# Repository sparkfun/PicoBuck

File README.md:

PicoBuck LED Driver
===================

[  
*PicoBuck LED Driver (COM-11850)*](https://www.sparkfun.com/products/11850)

This breakout board allows you to control and blend 3 different LEDs on 3 different channels. 

Repository Contents
-------------------
* **/Hardware** - All Eagle design files (.brd, .sch, .STL)
* **/Production** - Test bed files and production panel files

License Information
-------------------
The hardware is released under [Creative Commons Share-alike 3.0](http://creativecommons.org/licenses/by-sa/3.0/).  
All other code is open source so please feel free to do anything you want with it; you buy me a beer if you use this and we meet someday ([Beerware license](http://en.wikipedia.org/wiki/Beerware)).
 
 -> This was a collaboration with Ethan Zonca<-

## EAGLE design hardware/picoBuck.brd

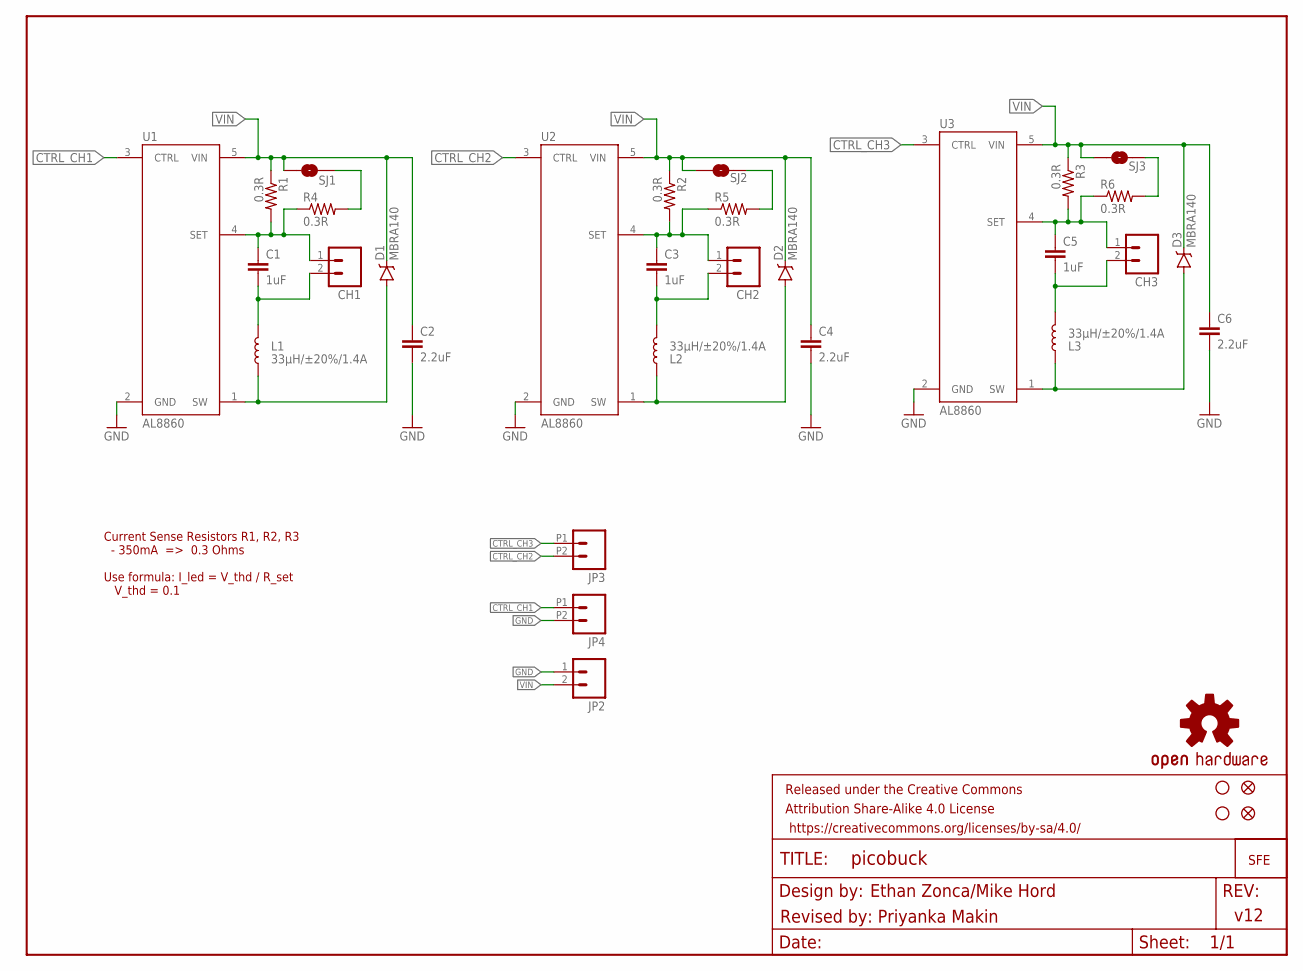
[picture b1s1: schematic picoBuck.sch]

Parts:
C1, C3, C5: 1uF; 0805
C2, C4, C6: 2.2uF; 0805
CH1, CH2, CH3: CONN_023.5MM_LOCK; SCREWTERMINAL-3.5MM-2_LOCK
D1, D2, D3: MBRA140; SMA-DIODE
FID1, FID2: FIDUCIALUFIDUCIAL; MICRO-FIDUCIAL
FRAME1: FRAME-LETTER; CREATIVE_COMMONS
JP2: CONN_023.5MM_LOCK; SCREWTERMINAL-3.5MM-2_LOCK
JP3, JP4: M022.54MM_SCREWTERM; 1X02_2.54_SCREWTERM@1
L1, L2, L3: 33µH/±20%/1.4A; SRN6045
LOGO1: OSHW-LOGOS; OSHW-LOGO-S
LOGO2: LOGO-SFENEW; SFE-NEW-WEBLOGO
R1, R2, R3, R4, R5, R6: 0.3R; 0805
SJ1, SJ2, SJ3: JUMPER-SMT_2_NO_NO-SILK; SMT-JUMPER_2_NO_NO-SILK
STANDOFF1, STANDOFF2: STAND-OFF
U1, U2, U3: AL8860; SOT23-5

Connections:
CTRL_CH1: JP4.P1 (1), U1.3 (CTRL)
CTRL_CH2: JP3.P2 (2), U2.3 (CTRL)
CTRL_CH3: JP3.P1 (1), U3.3 (CTRL)
GND: C2.2, C4.2, C6.2, JP2.1, JP4.P2 (2), U1.2 (GND), U2.2 (GND), U3.2 (GND)
IND1-1: D1.A, L1.1, U1.1 (SW)
IND2-1: D2.A, L2.1, U2.1 (SW)
IND3-1: D3.A, L3.1, U3.1 (SW)
unnamed: C5.1, CH3.1, R3.2, R6.1, U3.4 (SET)
unnamed: R4.2, SJ1.2
unnamed: R5.2, SJ2.2
unnamed: C1.2, CH1.2, L1.2
unnamed: R6.2, SJ3.2
unnamed: C3.2, CH2.2, L2.2
unnamed: C1.1, CH1.1, R1.2, R4.1, U1.4 (SET)
unnamed: C3.1, CH2.1, R2.2, R5.1, U2.4 (SET)
unnamed: C5.2, CH3.2, L3.2
VIN: C2.1, C4.1, C6.1, D1.C, D2.C, D3.C, JP2.2, R1.1, R2.1, R3.1, SJ1.1, SJ2.1, SJ3.1, U1.5 (VIN), U2.5 (VIN), U3.5 (VIN)

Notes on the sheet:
Current Sense Resistors R1, R2, R3 - 350mA => 0.3 Ohms Use formula: I_led = V_thd / R_set V_thd = 0.1
v12
Ethan Zonca/Mike Hord
Revised by: Priyanka Makin

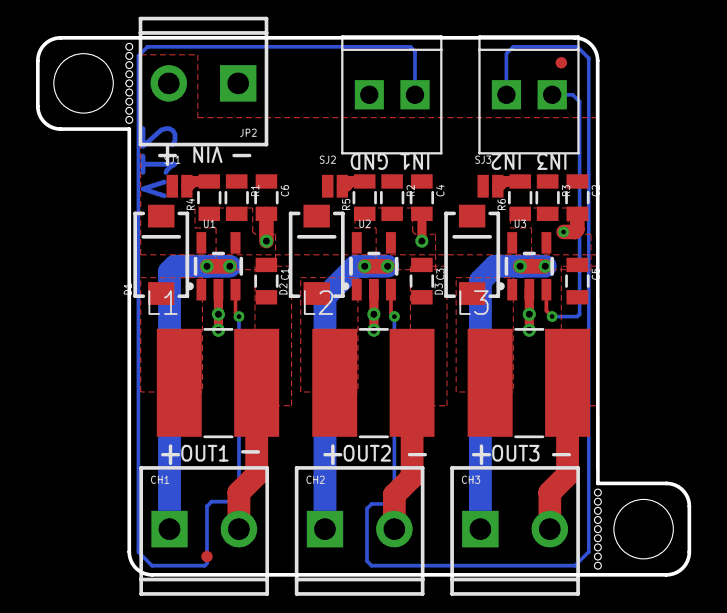
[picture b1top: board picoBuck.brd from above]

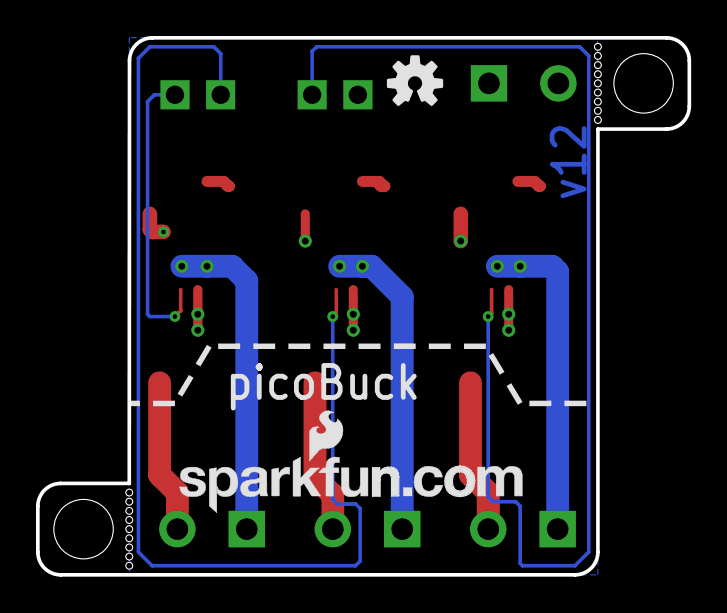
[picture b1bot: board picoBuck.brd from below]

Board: 2 copper layers, 36.2 x 29.8 mm, 37 parts (2 on the bottom side), 17 nets.

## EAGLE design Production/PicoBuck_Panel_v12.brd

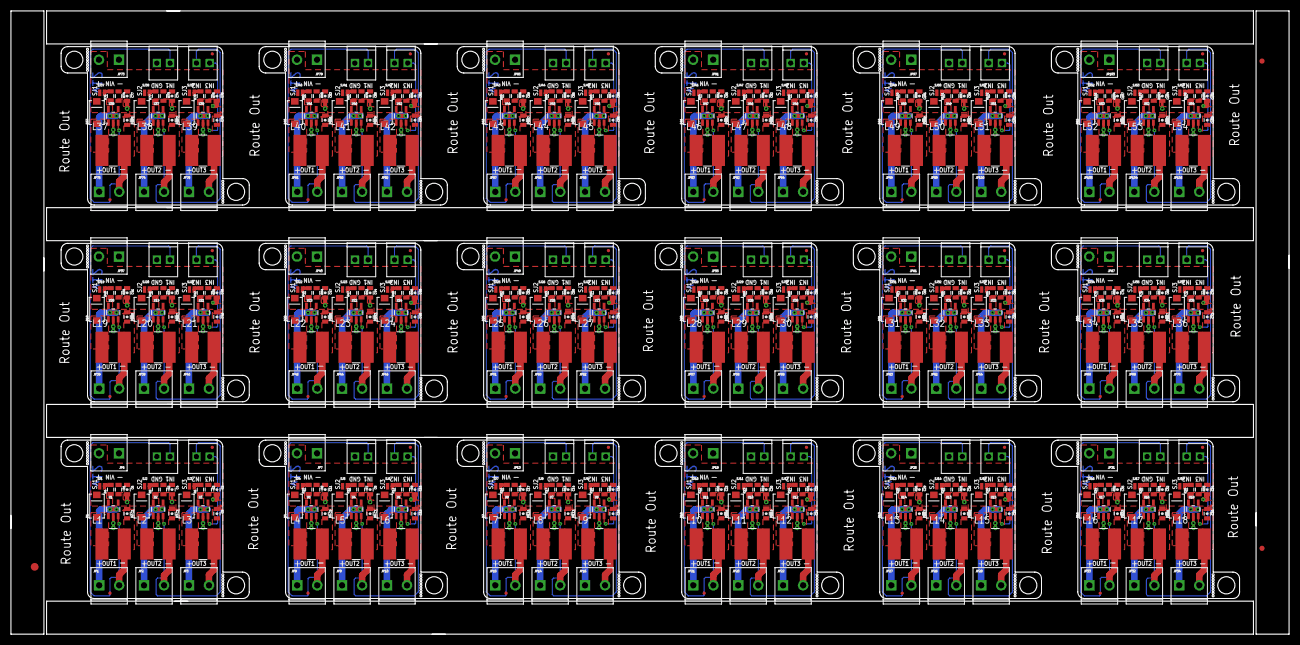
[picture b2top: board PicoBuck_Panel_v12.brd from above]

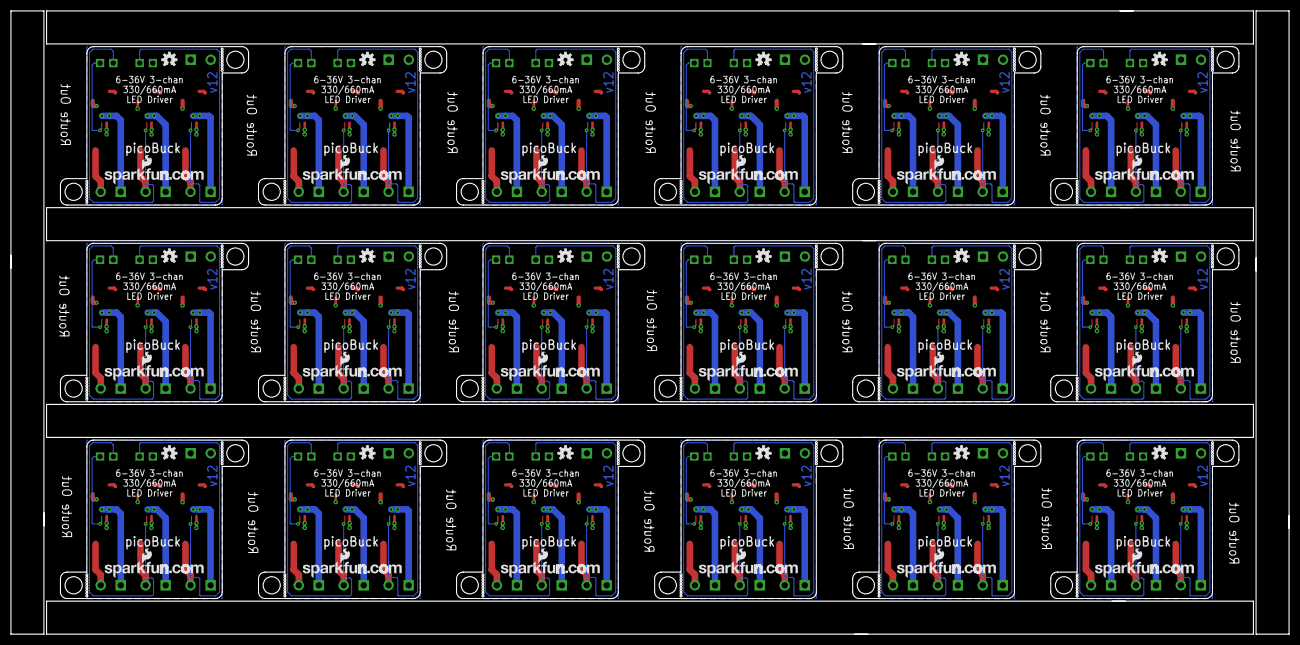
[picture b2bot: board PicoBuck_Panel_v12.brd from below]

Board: 2 copper layers, 245.9 x 119.9 mm, 651 parts (36 on the bottom side), 306 nets.

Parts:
C1, C3, C5, C7, C9, C12, C13, C15, C18, C19, C21, C24, C25, C27, C30, C31, C33, C36, C37, C39, C42, C43, C45, C48, C49, C51, C54, C55, C57, C60, C61, C63, C66, C67, C69, C72, C73, C75, C78, C79, C81, C84, C85, C87, C90, C91, C93, C96, C97, C99, C102, C103, C105, C108: 1.0uF; 0805-CAP
C2, C4, C6, C8, C10, C11, C14, C16, C17, C20, C22, C23, C26, C28, C29, C32, C34, C35, C38, C40, C41, C44, C46, C47, C50, C52, C53, C56, C58, C59, C62, C64, C65, C68, C70, C71, C74, C76, C77, C80, C82, C83, C86, C88, C89, C92, C94, C95, C98, C100, C101, C104, C106, C107: 2.2uF; 0805-CAP
D1, D2, D3, D4, D5, D6, D7, D8, D9, D10, D11, D12, D13, D14, D15, D16, D17, D18, D19, D20, D21, D22, D23, D24, D25, D26, D27, D28, D29, D30, D31, D32, D33, D34, D35, D36, D37, D38, D39, D40, D41, D42, D43, D44, D45, D46, D47, D48, D49, D50, D51, D52, D53, D54: MBRA140; SMA-DIODE
E$1: FIDUCIAL-1.5X3
E$9, E$10: FIDUCIAL-1X2
FID1, FID2, FID3, FID4, FID5, FID6, FID7, FID8, FID9, FID10, FID11, FID12, FID13, FID14, FID15, FID16, FID17, FID18, FID19, FID20, FID21, FID22, FID23, FID24, FID25, FID26, FID27, FID28, FID29, FID30, FID31, FID32, FID33, FID34, FID35, FID36: FIDUCIALUFIDUCIAL; MICRO-FIDUCIAL
JP1, JP2, JP3, JP6, JP7, JP8, JP9, JP10, JP13, JP14, JP15, JP16, JP19, JP20, JP21, JP22, JP25, JP26, JP27, JP28, JP31, JP32, JP33, JP34, JP37, JP38, JP39, JP40, JP43, JP44, JP45, JP46, JP49, JP50, JP51, JP52, JP55, JP56, JP57, JP58, JP61, JP62, JP63, JP64, JP67, JP68, JP69, JP70, JP73, JP74, JP75, JP76, JP79, JP80, JP81, JP82, JP85, JP86, JP87, JP88, JP91, JP92, JP93, JP94, JP97, JP98, JP99, JP100, JP103, JP104, JP105, JP106: SCREWTERMINAL-3.5MM-2_LOCK
JP4, JP5, JP11, JP12, JP17, JP18, JP23, JP24, JP29, JP30, JP35, JP36, JP41, JP42, JP47, JP48, JP53, JP54, JP59, JP60, JP65, JP66, JP71, JP72, JP77, JP78, JP83, JP84, JP89, JP90, JP95, JP96, JP101, JP102, JP107, JP108: M022.54MM_SCREWTERM; 1X02_2.54_SCREWTERM
L1, L2, L3, L4, L5, L6, L7, L8, L9, L10, L11, L12, L13, L14, L15, L16, L17, L18, L19, L20, L21, L22, L23, L24, L25, L26, L27, L28, L29, L30, L31, L32, L33, L34, L35, L36, L37, L38, L39, L40, L41, L42, L43, L44, L45, L46, L47, L48, L49, L50, L51, L52, L53, L54: 33uH; SRN6045
LOGO1, LOGO3, LOGO5, LOGO7, LOGO9, LOGO11, LOGO13, LOGO15, LOGO17, LOGO19, LOGO21, LOGO23, LOGO25, LOGO27, LOGO29, LOGO31, LOGO33, LOGO35: OSHW-LOGOS; OSHW-LOGO-S
LOGO2, LOGO4, LOGO6, LOGO8, LOGO10, LOGO12, LOGO14, LOGO16, LOGO18, LOGO20, LOGO22, LOGO24, LOGO26, LOGO28, LOGO30, LOGO32, LOGO34, LOGO36: LOGO-SFENEW; SFE-NEW-WEBLOGO
R1, R2, R3, R4, R5, R6, R7, R8, R9, R10, R11, R12, R13, R14, R15, R16, R17, R18, R19, R20, R21, R22, R23, R24, R25, R26, R27, R28, R29, R30, R31, R32, R33, R34, R35, R36, R37, R38, R39, R40, R41, R42, R43, R44, R45, R46, R47, R48, R49, R50, R51, R52, R53, R54, R55, R56, R57, R58, R59, R60, R61, R62, R63, R64, R65, R66, R67, R68, R69, R70, R71, R72, R73, R74, R75, R76, R77, R78, R79, R80, R81, R82, R83, R84, R85, R86, R87, R88, R89, R90, R91, R92, R93, R94, R95, R96, R97, R98, R99, R100, R101, R102, R103, R104, R105, R106, R107, R108: 0.3; 0805
SJ1, SJ2, SJ3, SJ4, SJ5, SJ6, SJ7, SJ8, SJ9, SJ10, SJ11, SJ12, SJ13, SJ14, SJ15, SJ16, SJ17, SJ18, SJ19, SJ20, SJ21, SJ22, SJ23, SJ24, SJ25, SJ26, SJ27, SJ28, SJ29, SJ30, SJ31, SJ32, SJ33, SJ34, SJ35, SJ36, SJ37, SJ38, SJ39, SJ40, SJ41, SJ42, SJ43, SJ44, SJ45, SJ46, SJ47, SJ48, SJ49, SJ50, SJ51, SJ52, SJ53, SJ54: JUMPER-PAD-2-NO; PAD-JUMPER-2-NO_NO_SILK
STANDOFF1, STANDOFF2, STANDOFF3, STANDOFF4, STANDOFF5, STANDOFF6, STANDOFF7, STANDOFF8, STANDOFF9, STANDOFF10, STANDOFF11, STANDOFF12, STANDOFF13, STANDOFF14, STANDOFF15, STANDOFF16, STANDOFF17, STANDOFF18, STANDOFF19, STANDOFF20, STANDOFF21, STANDOFF22, STANDOFF23, STANDOFF24, STANDOFF25, STANDOFF26, STANDOFF27, STANDOFF28, STANDOFF29, STANDOFF30, STANDOFF31, STANDOFF32, STANDOFF33, STANDOFF34, STANDOFF35, STANDOFF36: STAND-OFF
U1, U2, U3, U4, U5, U6, U7, U8, U9, U10, U11, U12, U13, U14, U15, U16, U17, U18, U19, U20, U21, U22, U23, U24, U25, U26, U27, U28, U29, U30, U31, U32, U33, U34, U35, U36, U37, U38, U39, U40, U41, U42, U43, U44, U45, U46, U47, U48, U49, U50, U51, U52, U53, U54: AL8805WS; SOT23-5

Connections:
CTRL_CH1: JP5.P1, U1.3
CTRL_CH2: JP4.P2, U2.3
CTRL_CH3: JP4.P1, U3.3
CTRL_CH4: JP12.P1, U5.3
CTRL_CH5: JP11.P2, U4.3
CTRL_CH6: JP11.P1, U6.3
CTRL_CH7: JP18.P1, U8.3
CTRL_CH8: JP17.P2, U7.3
CTRL_CH9: JP17.P1, U9.3
CTRL_CH10: JP24.P1, U11.3
CTRL_CH11: JP23.P2, U10.3
CTRL_CH12: JP23.P1, U12.3
CTRL_CH13: JP30.P1, U14.3
CTRL_CH14: JP29.P2, U13.3
CTRL_CH15: JP29.P1, U15.3
CTRL_CH16: JP36.P1, U17.3
CTRL_CH17: JP35.P2, U16.3
CTRL_CH18: JP35.P1, U18.3
CTRL_CH19: JP42.P1, U20.3
CTRL_CH20: JP41.P2, U19.3
CTRL_CH21: JP41.P1, U21.3
CTRL_CH22: JP48.P1, U23.3
CTRL_CH23: JP47.P2, U22.3
CTRL_CH24: JP47.P1, U24.3
CTRL_CH25: JP54.P1, U26.3
CTRL_CH26: JP53.P2, U25.3
CTRL_CH27: JP53.P1, U27.3
CTRL_CH28: JP60.P1, U29.3
CTRL_CH29: JP59.P2, U28.3
CTRL_CH30: JP59.P1, U30.3
CTRL_CH31: JP66.P1, U32.3
CTRL_CH32: JP65.P2, U31.3
CTRL_CH33: JP65.P1, U33.3
CTRL_CH34: JP72.P1, U35.3
CTRL_CH35: JP71.P2, U34.3
CTRL_CH36: JP71.P1, U36.3
CTRL_CH37: JP78.P1, U38.3
CTRL_CH38: JP77.P2, U37.3
CTRL_CH39: JP77.P1, U39.3
CTRL_CH40: JP84.P1, U41.3
CTRL_CH41: JP83.P2, U40.3
CTRL_CH42: JP83.P1, U42.3
CTRL_CH43: JP90.P1, U44.3
CTRL_CH44: JP89.P2, U43.3
CTRL_CH45: JP89.P1, U45.3
CTRL_CH46: JP96.P1, U47.3
CTRL_CH47: JP95.P2, U46.3
CTRL_CH48: JP95.P1, U48.3
CTRL_CH49: JP102.P1, U50.3
CTRL_CH50: JP101.P2, U49.3
CTRL_CH51: JP101.P1, U51.3
CTRL_CH52: JP108.P1, U53.3
CTRL_CH53: JP107.P2, U52.3
CTRL_CH54: JP107.P1, U54.3
GND: C2.2, C4.2, C6.2, JP5.P2, JP6.1, U1.2, U2.2, U3.2
GND1: C8.2, C10.2, C11.2, JP7.1, JP12.P2, U4.2, U5.2, U6.2
GND2: C14.2, C16.2, C17.2, JP13.1, JP18.P2, U7.2, U8.2, U9.2
GND3: C20.2, C22.2, C23.2, JP19.1, JP24.P2, U10.2, U11.2, U12.2
GND4: C26.2, C28.2, C29.2, JP25.1, JP30.P2, U13.2, U14.2, U15.2
GND5: C32.2, C34.2, C35.2, JP31.1, JP36.P2, U16.2, U17.2, U18.2
GND6: C38.2, C40.2, C41.2, JP37.1, JP42.P2, U19.2, U20.2, U21.2
GND7: C44.2, C46.2, C47.2, JP43.1, JP48.P2, U22.2, U23.2, U24.2
GND8: C50.2, C52.2, C53.2, JP49.1, JP54.P2, U25.2, U26.2, U27.2
GND9: C56.2, C58.2, C59.2, JP55.1, JP60.P2, U28.2, U29.2, U30.2
GND10: C62.2, C64.2, C65.2, JP61.1, JP66.P2, U31.2, U32.2, U33.2
GND11: C68.2, C70.2, C71.2, JP67.1, JP72.P2, U34.2, U35.2, U36.2
GND12: C74.2, C76.2, C77.2, JP73.1, JP78.P2, U37.2, U38.2, U39.2
GND13: C80.2, C82.2, C83.2, JP79.1, JP84.P2, U40.2, U41.2, U42.2
GND14: C86.2, C88.2, C89.2, JP85.1, JP90.P2, U43.2, U44.2, U45.2
GND15: C92.2, C94.2, C95.2, JP91.1, JP96.P2, U46.2, U47.2, U48.2
GND16: C98.2, C100.2, C101.2, JP97.1, JP102.P2, U49.2, U50.2, U51.2
GND17: C104.2, C106.2, C107.2, JP103.1, JP108.P2, U52.2, U53.2, U54.2
IND1-1: D1.A, L1.1, U1.1
IND1-2: D4.A, L4.1, U5.1
IND1-3: D7.A, L7.1, U8.1
IND1-4: D10.A, L10.1, U11.1
IND1-5: D13.A, L13.1, U14.1
IND1-6: D16.A, L16.1, U17.1
IND1-7: D19.A, L19.1, U20.1
IND1-8: D22.A, L22.1, U23.1
IND1-9: D25.A, L25.1, U26.1
IND1-10: D28.A, L28.1, U29.1
IND1-11: D31.A, L31.1, U32.1
IND1-12: D34.A, L34.1, U35.1
IND1-13: D37.A, L37.1, U38.1
IND1-14: D40.A, L40.1, U41.1
IND1-15: D43.A, L43.1, U44.1
IND1-16: D46.A, L46.1, U47.1
IND1-17: D49.A, L49.1, U50.1
IND1-18: D52.A, L52.1, U53.1
IND2-1: D2.A, L2.1, U2.1
IND2-2: D5.A, L5.1, U4.1
IND2-3: D8.A, L8.1, U7.1
IND2-4: D11.A, L11.1, U10.1
IND2-5: D14.A, L14.1, U13.1
IND2-6: D17.A, L17.1, U16.1
IND2-7: D20.A, L20.1, U19.1
IND2-8: D23.A, L23.1, U22.1
IND2-9: D26.A, L26.1, U25.1
IND2-10: D29.A, L29.1, U28.1
IND2-11: D32.A, L32.1, U31.1
IND2-12: D35.A, L35.1, U34.1
IND2-13: D38.A, L38.1, U37.1
IND2-14: D41.A, L41.1, U40.1
IND2-15: D44.A, L44.1, U43.1
IND2-16: D47.A, L47.1, U46.1
IND2-17: D50.A, L50.1, U49.1
IND2-18: D53.A, L53.1, U52.1
IND3-1: D3.A, L3.1, U3.1
IND3-2: D6.A, L6.1, U6.1
IND3-3: D9.A, L9.1, U9.1
IND3-4: D12.A, L12.1, U12.1
IND3-5: D15.A, L15.1, U15.1
IND3-6: D18.A, L18.1, U18.1
IND3-7: D21.A, L21.1, U21.1
IND3-8: D24.A, L24.1, U24.1
IND3-9: D27.A, L27.1, U27.1
IND3-10: D30.A, L30.1, U30.1
IND3-11: D33.A, L33.1, U33.1
IND3-12: D36.A, L36.1, U36.1
IND3-13: D39.A, L39.1, U39.1
IND3-14: D42.A, L42.1, U42.1
IND3-15: D45.A, L45.1, U45.1
IND3-16: D48.A, L48.1, U48.1
IND3-17: D51.A, L51.1, U51.1
IND3-18: D54.A, L54.1, U54.1
unnamed: C5.1, JP3.1, R3.2, R6.1, U3.4
unnamed: R4.2, SJ1.2
unnamed: R5.2, SJ2.2
unnamed: C7.2, JP8.2, L5.2
unnamed: C1.2, JP1.2, L1.2
unnamed: C7.1, JP8.1, R7.2, R11.1, U4.4
unnamed: R6.2, SJ3.2
unnamed: C9.2, JP9.2, L4.2
unnamed: C3.2, JP2.2, L2.2
unnamed: C9.1, JP9.1, R8.2, R10.1, U5.4
unnamed: C1.1, JP1.1, R1.2, R4.1, U1.4
unnamed: C12.2, JP10.2, L6.2
unnamed: C3.1, JP2.1, R2.2, R5.1, U2.4
unnamed: R10.2, SJ4.2
unnamed: R11.2, SJ5.2
unnamed: C5.2, JP3.2, L3.2
unnamed: R12.2, SJ6.2
unnamed: C12.1, JP10.1, R9.2, R12.1, U6.4
unnamed: C13.2, JP14.2, L8.2
unnamed: C13.1, JP14.1, R13.2, R17.1, U7.4
unnamed: C15.2, JP15.2, L7.2
unnamed: C15.1, JP15.1, R14.2, R16.1, U8.4
unnamed: C18.2, JP16.2, L9.2
unnamed: R16.2, SJ7.2
unnamed: R17.2, SJ8.2
unnamed: R18.2, SJ9.2
unnamed: C18.1, JP16.1, R15.2, R18.1, U9.4
unnamed: C19.2, JP20.2, L11.2
unnamed: C19.1, JP20.1, R19.2, R23.1, U10.4
unnamed: C21.2, JP21.2, L10.2
unnamed: C21.1, JP21.1, R20.2, R22.1, U11.4
unnamed: C24.2, JP22.2, L12.2
unnamed: R22.2, SJ10.2
unnamed: R23.2, SJ11.2
unnamed: R24.2, SJ12.2
unnamed: C24.1, JP22.1, R21.2, R24.1, U12.4
unnamed: C25.2, JP26.2, L14.2
unnamed: C25.1, JP26.1, R25.2, R29.1, U13.4
unnamed: C27.2, JP27.2, L13.2
unnamed: C27.1, JP27.1, R26.2, R28.1, U14.4
unnamed: C30.2, JP28.2, L15.2
unnamed: R28.2, SJ13.2
unnamed: R29.2, SJ14.2
unnamed: R30.2, SJ15.2
unnamed: C30.1, JP28.1, R27.2, R30.1, U15.4
unnamed: C31.2, JP32.2, L17.2
unnamed: C31.1, JP32.1, R31.2, R35.1, U16.4
unnamed: C33.2, JP33.2, L16.2
unnamed: C33.1, JP33.1, R32.2, R34.1, U17.4
unnamed: C36.2, JP34.2, L18.2
unnamed: R34.2, SJ16.2
unnamed: R35.2, SJ17.2
unnamed: R36.2, SJ18.2
unnamed: C36.1, JP34.1, R33.2, R36.1, U18.4
unnamed: C37.2, JP38.2, L20.2
unnamed: C37.1, JP38.1, R37.2, R41.1, U19.4
unnamed: C39.2, JP39.2, L19.2
unnamed: C39.1, JP39.1, R38.2, R40.1, U20.4
unnamed: C42.2, JP40.2, L21.2
unnamed: R40.2, SJ19.2
unnamed: R41.2, SJ20.2
unnamed: R42.2, SJ21.2
unnamed: C42.1, JP40.1, R39.2, R42.1, U21.4
unnamed: C43.2, JP44.2, L23.2
unnamed: C43.1, JP44.1, R43.2, R47.1, U22.4
unnamed: C45.2, JP45.2, L22.2
unnamed: C45.1, JP45.1, R44.2, R46.1, U23.4
unnamed: C48.2, JP46.2, L24.2
unnamed: R46.2, SJ22.2
unnamed: R47.2, SJ23.2
unnamed: R48.2, SJ24.2
unnamed: C48.1, JP46.1, R45.2, R48.1, U24.4
unnamed: C49.2, JP50.2, L26.2
unnamed: C49.1, JP50.1, R49.2, R53.1, U25.4
unnamed: C51.2, JP51.2, L25.2
unnamed: C51.1, JP51.1, R50.2, R52.1, U26.4
unnamed: C54.2, JP52.2, L27.2
unnamed: R52.2, SJ25.2
unnamed: R53.2, SJ26.2
unnamed: R54.2, SJ27.2
unnamed: C54.1, JP52.1, R51.2, R54.1, U27.4
unnamed: C55.2, JP56.2, L29.2
unnamed: C55.1, JP56.1, R55.2, R59.1, U28.4
unnamed: C57.2, JP57.2, L28.2
unnamed: C57.1, JP57.1, R56.2, R58.1, U29.4
unnamed: C60.2, JP58.2, L30.2
unnamed: R58.2, SJ28.2
unnamed: R59.2, SJ29.2
unnamed: R60.2, SJ30.2
unnamed: C60.1, JP58.1, R57.2, R60.1, U30.4
unnamed: C61.2, JP62.2, L32.2
unnamed: C61.1, JP62.1, R61.2, R65.1, U31.4
unnamed: C63.2, JP63.2, L31.2
unnamed: C63.1, JP63.1, R62.2, R64.1, U32.4
unnamed: C66.2, JP64.2, L33.2
unnamed: R64.2, SJ31.2
unnamed: R65.2, SJ32.2
unnamed: R66.2, SJ33.2
unnamed: C66.1, JP64.1, R63.2, R66.1, U33.4
unnamed: C67.2, JP68.2, L35.2
unnamed: C67.1, JP68.1, R67.2, R71.1, U34.4
unnamed: C69.2, JP69.2, L34.2
unnamed: C69.1, JP69.1, R68.2, R70.1, U35.4
unnamed: C72.2, JP70.2, L36.2
unnamed: R70.2, SJ34.2
unnamed: R71.2, SJ35.2
unnamed: R72.2, SJ36.2
unnamed: C72.1, JP70.1, R69.2, R72.1, U36.4
unnamed: C73.2, JP74.2, L38.2
unnamed: C73.1, JP74.1, R73.2, R77.1, U37.4
unnamed: C75.2, JP75.2, L37.2
unnamed: C75.1, JP75.1, R74.2, R76.1, U38.4
unnamed: C78.2, JP76.2, L39.2
unnamed: R76.2, SJ37.2
unnamed: R77.2, SJ38.2
unnamed: R78.2, SJ39.2
unnamed: C78.1, JP76.1, R75.2, R78.1, U39.4
unnamed: C79.2, JP80.2, L41.2
unnamed: C79.1, JP80.1, R79.2, R83.1, U40.4
unnamed: C81.2, JP81.2, L40.2
unnamed: C81.1, JP81.1, R80.2, R82.1, U41.4
unnamed: C84.2, JP82.2, L42.2
unnamed: R82.2, SJ40.2
unnamed: R83.2, SJ41.2
unnamed: R84.2, SJ42.2
unnamed: C84.1, JP82.1, R81.2, R84.1, U42.4
unnamed: C85.2, JP86.2, L44.2
unnamed: C85.1, JP86.1, R85.2, R89.1, U43.4
unnamed: C87.2, JP87.2, L43.2
unnamed: C87.1, JP87.1, R86.2, R88.1, U44.4
unnamed: C90.2, JP88.2, L45.2
unnamed: R88.2, SJ43.2
unnamed: R89.2, SJ44.2
unnamed: R90.2, SJ45.2
unnamed: C90.1, JP88.1, R87.2, R90.1, U45.4
unnamed: C91.2, JP92.2, L47.2
unnamed: C91.1, JP92.1, R91.2, R95.1, U46.4
unnamed: C93.2, JP93.2, L46.2
unnamed: C93.1, JP93.1, R92.2, R94.1, U47.4
unnamed: C96.2, JP94.2, L48.2
unnamed: R94.2, SJ46.2
unnamed: R95.2, SJ47.2
unnamed: R96.2, SJ48.2
unnamed: C96.1, JP94.1, R93.2, R96.1, U48.4
unnamed: C97.2, JP98.2, L50.2
unnamed: C97.1, JP98.1, R97.2, R101.1, U49.4
unnamed: C99.2, JP99.2, L49.2
unnamed: C99.1, JP99.1, R98.2, R100.1, U50.4
unnamed: C102.2, JP100.2, L51.2
unnamed: R100.2, SJ49.2
unnamed: R101.2, SJ50.2
unnamed: R102.2, SJ51.2
unnamed: C102.1, JP100.1, R99.2, R102.1, U51.4
unnamed: C103.2, JP104.2, L53.2
unnamed: C103.1, JP104.1, R103.2, R107.1, U52.4
unnamed: C105.2, JP105.2, L52.2
unnamed: C105.1, JP105.1, R104.2, R106.1, U53.4
unnamed: C108.2, JP106.2, L54.2
unnamed: R106.2, SJ52.2
unnamed: R107.2, SJ53.2
unnamed: R108.2, SJ54.2
unnamed: C108.1, JP106.1, R105.2, R108.1, U54.4
VIN: C2.1, C4.1, C6.1, D1.C, D2.C, D3.C, JP6.2, R1.1, R2.1, R3.1, SJ1.1, SJ2.1, SJ3.1, U1.5, U2.5, U3.5
VIN1: C8.1, C10.1, C11.1, D4.C, D5.C, D6.C, JP7.2, R7.1, R8.1, R9.1, SJ4.1, SJ5.1, SJ6.1, U4.5, U5.5, U6.5
VIN2: C14.1, C16.1, C17.1, D7.C, D8.C, D9.C, JP13.2, R13.1, R14.1, R15.1, SJ7.1, SJ8.1, SJ9.1, U7.5, U8.5, U9.5
VIN3: C20.1, C22.1, C23.1, D10.C, D11.C, D12.C, JP19.2, R19.1, R20.1, R21.1, SJ10.1, SJ11.1, SJ12.1, U10.5, U11.5, U12.5
VIN4: C26.1, C28.1, C29.1, D13.C, D14.C, D15.C, JP25.2, R25.1, R26.1, R27.1, SJ13.1, SJ14.1, SJ15.1, U13.5, U14.5, U15.5
VIN5: C32.1, C34.1, C35.1, D16.C, D17.C, D18.C, JP31.2, R31.1, R32.1, R33.1, SJ16.1, SJ17.1, SJ18.1, U16.5, U17.5, U18.5
VIN6: C38.1, C40.1, C41.1, D19.C, D20.C, D21.C, JP37.2, R37.1, R38.1, R39.1, SJ19.1, SJ20.1, SJ21.1, U19.5, U20.5, U21.5
VIN7: C44.1, C46.1, C47.1, D22.C, D23.C, D24.C, JP43.2, R43.1, R44.1, R45.1, SJ22.1, SJ23.1, SJ24.1, U22.5, U23.5, U24.5
VIN8: C50.1, C52.1, C53.1, D25.C, D26.C, D27.C, JP49.2, R49.1, R50.1, R51.1, SJ25.1, SJ26.1, SJ27.1, U25.5, U26.5, U27.5
VIN9: C56.1, C58.1, C59.1, D28.C, D29.C, D30.C, JP55.2, R55.1, R56.1, R57.1, SJ28.1, SJ29.1, SJ30.1, U28.5, U29.5, U30.5
VIN10: C62.1, C64.1, C65.1, D31.C, D32.C, D33.C, JP61.2, R61.1, R62.1, R63.1, SJ31.1, SJ32.1, SJ33.1, U31.5, U32.5, U33.5
VIN11: C68.1, C70.1, C71.1, D34.C, D35.C, D36.C, JP67.2, R67.1, R68.1, R69.1, SJ34.1, SJ35.1, SJ36.1, U34.5, U35.5, U36.5
VIN12: C74.1, C76.1, C77.1, D37.C, D38.C, D39.C, JP73.2, R73.1, R74.1, R75.1, SJ37.1, SJ38.1, SJ39.1, U37.5, U38.5, U39.5
VIN13: C80.1, C82.1, C83.1, D40.C, D41.C, D42.C, JP79.2, R79.1, R80.1, R81.1, SJ40.1, SJ41.1, SJ42.1, U40.5, U41.5, U42.5
VIN14: C86.1, C88.1, C89.1, D43.C, D44.C, D45.C, JP85.2, R85.1, R86.1, R87.1, SJ43.1, SJ44.1, SJ45.1, U43.5, U44.5, U45.5
VIN15: C92.1, C94.1, C95.1, D46.C, D47.C, D48.C, JP91.2, R91.1, R92.1, R93.1, SJ46.1, SJ47.1, SJ48.1, U46.5, U47.5, U48.5
VIN16: C98.1, C100.1, C101.1, D49.C, D50.C, D51.C, JP97.2, R97.1, R98.1, R99.1, SJ49.1, SJ50.1, SJ51.1, U49.5, U50.5, U51.5
VIN17: C104.1, C106.1, C107.1, D52.C, D53.C, D54.C, JP103.2, R103.1, R104.1, R105.1, SJ52.1, SJ53.1, SJ54.1, U52.5, U53.5, U54.5

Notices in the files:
parts and their libraries:
SparkFun-Aesthetics: Licensing: CC v3.0 Share-Alike You are welcome to use this library for commercial purposes.
SparkFun-Electromechanical: Licensing: Creative Commons ShareAlike 4.0 International - https://creativecommons.org/licenses/by-sa/4.0
